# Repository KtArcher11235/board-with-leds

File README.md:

# board-with-leds

yep! It's... It's board with leds

Behold the technolgical marvles in this simple project, instead of having 1 led it has 6.
As the most advanced PCB out there, it is unfortunately verrrrrry expensive to make, like 5 bucks.
And if you aren't convinced yet... Idk I'm bored.

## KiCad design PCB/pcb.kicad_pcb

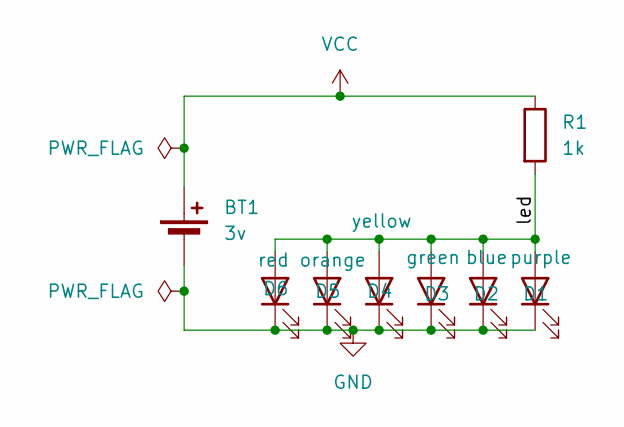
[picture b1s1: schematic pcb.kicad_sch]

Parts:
BT1: 3v; BatteryHolder_Keystone_1058_1x2032
D1: purple; LED_D5.0mm
D2: blue; LED_D5.0mm
D3: green; LED_D5.0mm
D4: yellow; LED_D5.0mm
D5: orange; LED_D5.0mm
D6: red; LED_D5.0mm
R1: 1k; R_Axial_DIN0309_L9.0mm_D3.2mm_P12.70mm_Horizontal

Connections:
/led: D1.2 (A), D2.2 (A), D3.2 (A), D4.2 (A), D5.2 (A), D6.2 (A), R1.2
GND: BT1.2 (-), D1.1 (K), D2.1 (K), D3.1 (K), D4.1 (K), D5.1 (K), D6.1 (K)
VCC: BT1.1 (+), R1.1

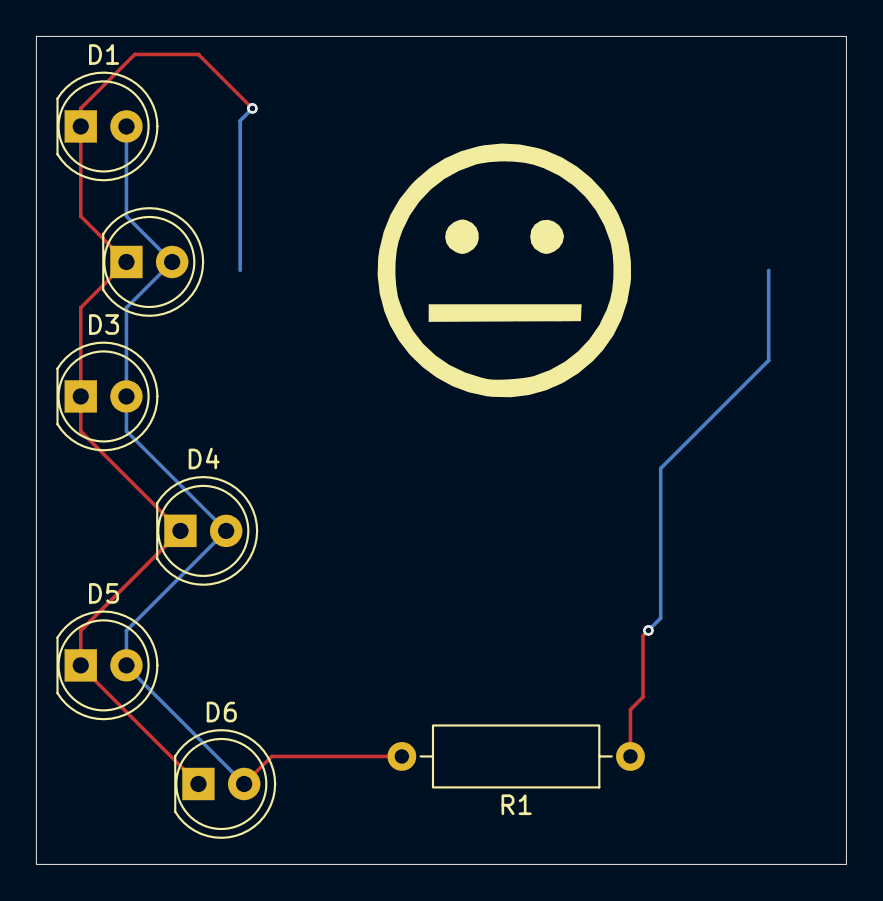
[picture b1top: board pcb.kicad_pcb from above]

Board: 2 copper layers, 45.0 x 46.0 mm, 8 parts (1 on the bottom side), 3 nets.

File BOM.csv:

"Reference","Qty","Value","DNP","Exclude from BOM","Exclude from Board","Footprint","Datasheet"
"BT1","1","3v","","","","Battery:BatteryHolder_Keystone_1058_1x2032","~"
"D1","1","purple","","","","LED_THT:LED_D5.0mm","~"
"D2","1","blue","","","","LED_THT:LED_D5.0mm","~"
"D3","1","green","","","","LED_THT:LED_D5.0mm","~"
"D4","1","yellow","","","","LED_THT:LED_D5.0mm","~"
"D5","1","orange","","","","LED_THT:LED_D5.0mm","~"
"D6","1","red","","","","LED_THT:LED_D5.0mm","~"
"R1","1","1k","","","","Resistor_THT:R_Axial_DIN0309_L9.0mm_D3.2mm_P12.70mm_Horizontal","~"

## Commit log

2025-11-21 Add PCB layout and schematic files
    Initial commit of KiCad PCB layout (.kicad_pcb), project (.kicad_pro), and schematic (.kicad_sch) files. Includes footprints for multiple LEDs and a custom logo.
2025-12-12 Enhance README with project details and humor
    Added a description of the project's features and cost.
2025-12-12 Rename pcb.csv to BOM.csv
    Renamed the file for improved clarity and consistency in naming conventions.
2025-12-12 Add 3D PCB and component models
    Added pcb.step (STEP format) and pcb.wrl (VRML format) files for the PCB and its components, enabling 3D visualization and integration with CAD tools.
2025-12-12 Add initial firmware script and instructions
    Added FirmwareInstalationInstructions.md with basic installation steps and a placeholder firmware.py script for the board.
